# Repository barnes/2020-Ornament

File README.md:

# 2020-Ornament
Simple PCB ornament

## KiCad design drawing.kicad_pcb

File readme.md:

## 2020 Ornament PCB 
This simple PCB is a quick and easy ornament to gift this season. Nothing but a battery, LEDs, current limiting resistor and a switch. Dead simple.

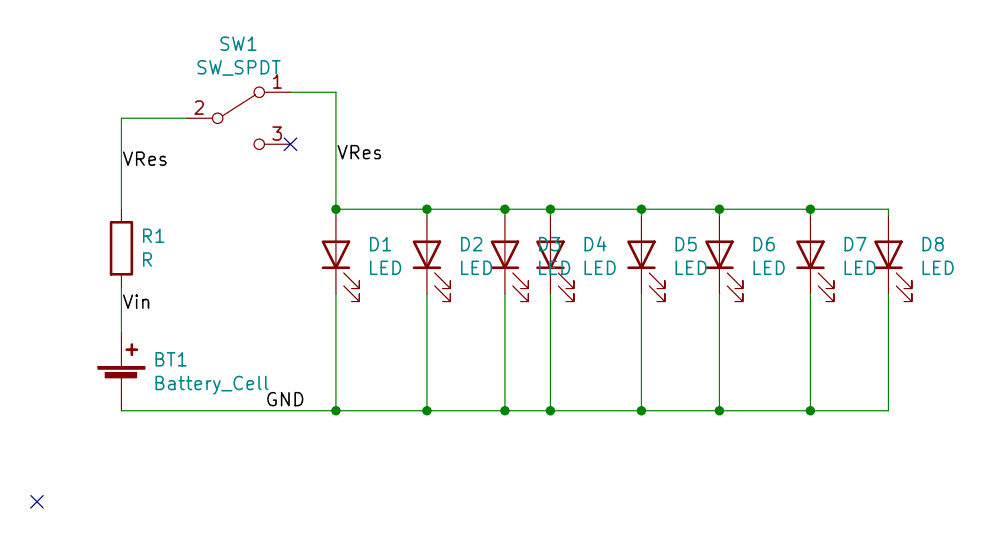
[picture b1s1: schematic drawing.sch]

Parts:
BT1: Battery_Cell; BatteryHolder_MPD_BC2003_1x2032
D1, D2, D3, D4, D5, D6, D7, D8: LED; LED_1206_3216Metric
R1: R; R_1206_3216Metric
SW1: SW_SPDT; SW_SPDT_PCM12

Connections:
/GND: BT1.2 (-), D1.1 (K), D2.1 (K), D3.1 (K), D4.1 (K), D5.1 (K), D6.1 (K), D7.1 (K), D8.1 (K)
/VRes: D1.2 (A), D2.2 (A), D3.2 (A), D4.2 (A), D5.2 (A), D6.2 (A), D7.2 (A), D8.2 (A), R1.1, SW1.1 (A), SW1.2 (B)
/Vin: BT1.1 (+), R1.2

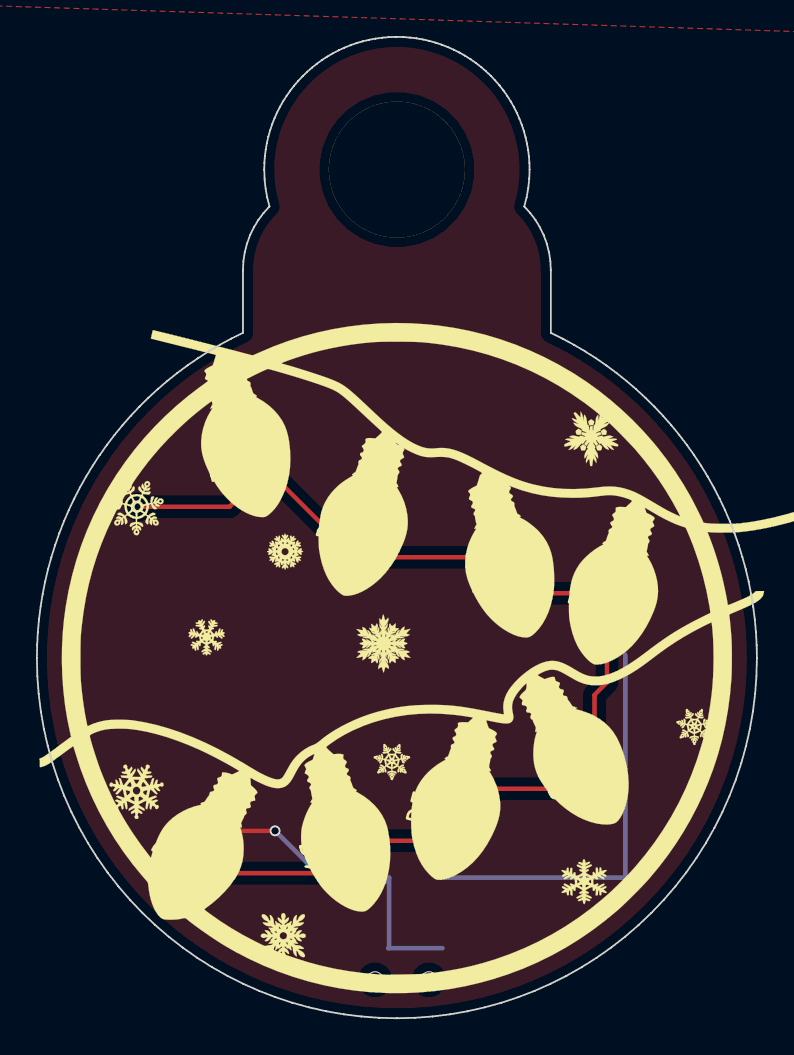
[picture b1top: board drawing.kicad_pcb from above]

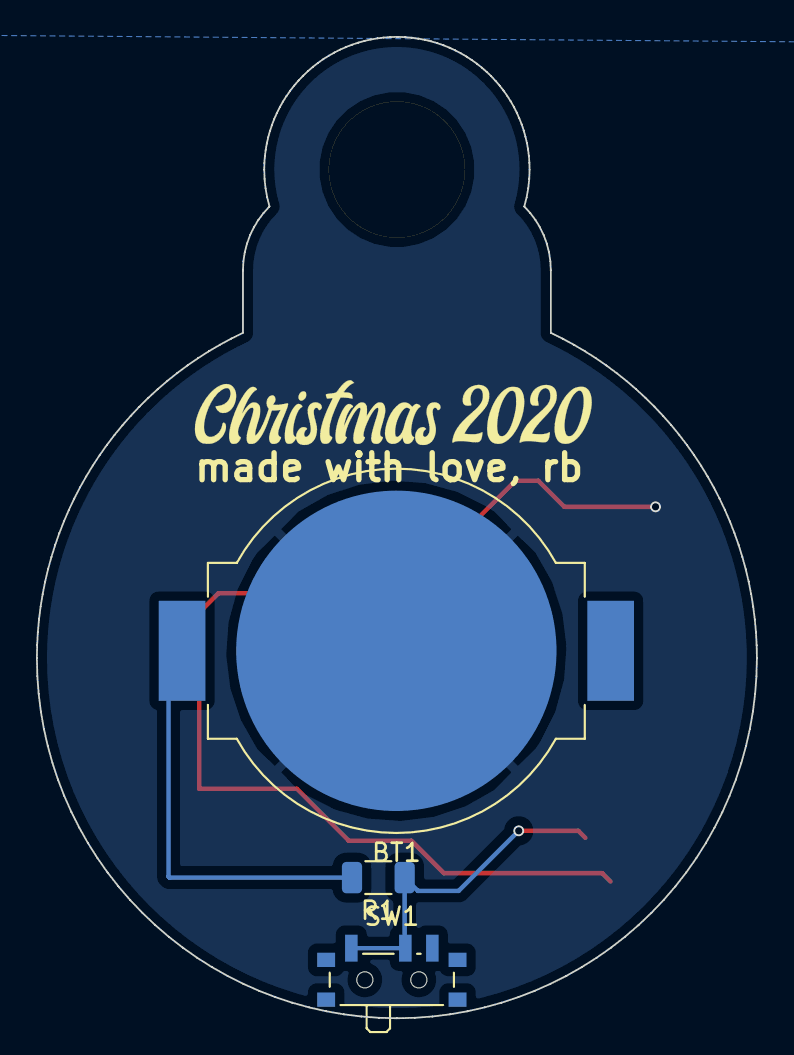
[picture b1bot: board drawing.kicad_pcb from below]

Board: 2 copper layers, 40.0 x 54.5 mm, 11 parts (3 on the bottom side), 3 nets.

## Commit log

2020-11-27 initial files, completed, fabricated and tested.
